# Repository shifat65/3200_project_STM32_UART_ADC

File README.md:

# STM32F103C6 Dual MCU Communication(UART) Project

## Overview

This project demonstrates UART communication, ADC threshold detection, timer-triggered transmissions, and external interrupt handling between two STM32F103C6 microcontrollers. The system is fully interrupt-driven and utilizes key peripherals including UART, ADC, Timers, SysTick, and GPIO.

## Features

### UART Communication (Between Two STM32F103C6 MCUs)
- **Transmit Indicator:** PA0 blinks when data is sent.
- **Receive Indicator:** PA1 blinks when data is received.
- **USART1 (PA9/PA10)** is used for UART communication.

### Timer-Based Data Transmission
- Timer triggers data transmission (values 0 to 3 cyclically) every 3 seconds.
- **Indicators:**
  - **PA4:** Displays the LSB of the transmitted data.
  - **PA7:** Displays the MSB of the transmitted data.

### Photoresistor Reading & Threshold Detection
- Reads analog input from a photoresistor connected to PB0.
- **High Threshold:** Turns ON PA5.
- **Low Threshold:** Turns OFF PA5 on the receiving MCU.

### External Interrupt Handling
- **PA2:** Configured for external interrupt input.
- On interrupt trigger via push button, a signal is sent to the other MCU.
- The second MCU toggles **PA6** in response.

## Hardware Used

- **2× STM32F103C6** microcontrollers (Blue Pill boards)
- **LEDs** (connected to GPIO pins for indication)
- **Photoresistor (LDR)** connected to PB0 for ADC input
- **Push Button** for triggering external interrupt on PA2
- **Breadboard** for prototyping
- **Jumper Wires** for connections
- **ST-Link Programmer** for flashing code

## STM32F103C6 Peripherals Used

- UART (USART1)
- ADC1 with Analog Watchdog
- General-purpose Timer (TIM2)
- SysTick Timer
- External Interrupt (EXTI2)
- GPIO (Input/Output)
- All operations are interrupt-driven

## Pin Configuration

| Pin    | Purpose                                  | Configuration                | CNF[1:0] + MODE[1:0] |
|--------|------------------------------------------|------------------------------|----------------------|
| PA0    | TX Indicator (Blink)                     | GPIO Output Push-Pull        | 0011                 |
| PA1    | RX Indicator (Blink)                     | GPIO Output Push-Pull        | 0011                 |
| PA2    | External Interrupt Input (Push Button)   | GPIO Input Pull-up/down      | 1000                 |
| PA4    | LSB Indicator of Sent Data               | GPIO Output Push-Pull        | 0011                 |
| PA5    | ADC Threshold Output                     | GPIO Output Push-Pull        | 0011                 |
| PA6    | External Interrupt Response (Toggle)     | GPIO Output Push-Pull        | 0011                 |
| PA7    | MSB Indicator of Sent Data               | GPIO Output Push-Pull        | 0011                 |
| PA9    | UART TX (USART1_TX)                      | Alternate Function Push-Pull | 1011                 |
| PA10   | UART RX (USART1_RX)                      | Input Floating               | 0100                 |
| PB0    | Photoresistor Input (ADC)                | Analog Input                 | 0000                 |

## Project Structure

### Initialization Functions

1. `void En_clock(void)`  
   Enables peripheral clocks for USART1, GPIO ports, TIM2, and ADC1.

2. `void gpio_setup(void)`  
   Configures GPIOs for UART, ADC input, external interrupts, and indicators.

3. `void systick_config(void)`  
   Configures SysTick for 1 ms tick using a 72 MHz system clock.

4. `void delay_ms(void)` and `void delay(uint32_t count)`  
   Delay utilities based on SysTick polling.

5. `void Uart1_config(void)`  
   Initializes USART1:
   - Baud Rate: 9600
   - Enables Tx, Rx, and RXNE interrupt
   - GPIO setup for PA9/PA10

6. `void ADC_config(void)`  
   Sets up ADC1 with:
   - Channel 8 (PB0)
   - Continuous conversion
   - Analog watchdog with threshold interrupts

7. `void timer_config(void)`  
   Configures TIM2:
   - Prescaler: 7200
   - Auto-reload: 50000
   - Triggers interrupt every 5 seconds

### Interrupt Handlers

- `void TIM2_IRQHandler(void)`  
  - Sends data via UART
  - Toggles PA0
  - Updates PA4 and PA7 to show LSB/MSB

- `void USART1_IRQHandler(void)`  
  - Handles received UART data
  - Updates GPIO indicators based on data

- `void ADC1_2_IRQHandler(void)`  
  - Compares ADC value to high/low thresholds
  - Sends specific character over UART depending on value range

- `void EXTI2_IRQHandler(void)`  
  - Responds to external interrupt on PA2
  - Sends a signal via UART
  - Toggles PA0

### Main Function

- `int main(void)`
  - Calls all setup functions
  - Enters an infinite loop
  - All runtime operations are interrupt-driven

## Circuit Diagram

## Build & Flash Instructions (Keil µVision 5)

1. Open the project in **Keil µVision 5** (`.uvprojx` file).
2. Set the target device to **STM32F103C6**.
3. Ensure correct startup file and system clock settings (72 MHz).
4. Build the project: **Project > Build Target** or press **F7**.
5. Connect the board using **ST-Link**.
6. Flash the firmware: **Flash > Download** or press **Ctrl + F8**.

### Tools Required

- Keil µVision 5 IDE
- STM32F1 Series Device Pack (via Keil Pack Installer)
- ST-Link USB Programmer 
- Optional: Logic analyzer or oscilloscope for UART debug

## Notes

- Use the same UART settings on both MCUs.
- Connect both boards with a common GND.
- Push button should be debounced or used with delay to avoid noise.
- ADC thresholds should match the characteristics of your photoresistor and ambient light conditions.

## License

This project is created for academic and educational purposes under the CSE 3200 course. No open-source license is currently applied.

## Author

*Syed Shifat E Rahman*

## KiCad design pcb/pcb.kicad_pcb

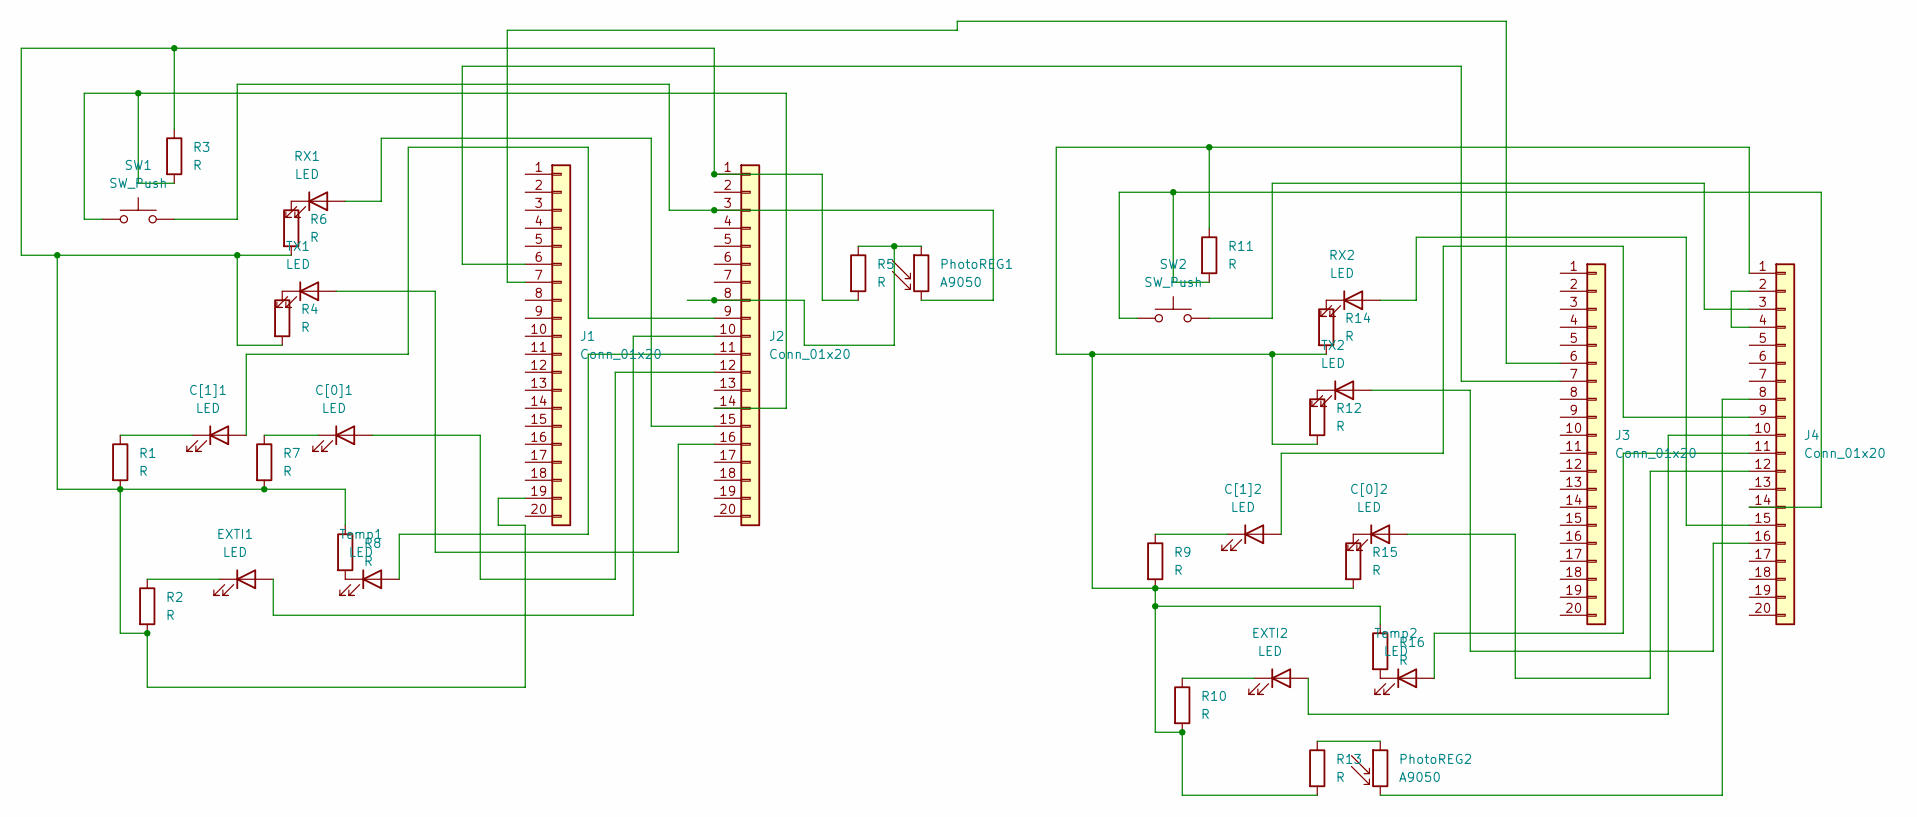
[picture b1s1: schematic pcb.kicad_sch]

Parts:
C[0]1, C[0]2, C[1]1, C[1]2: LED; LED_D3.0mm
EXTI1, EXTI2: LED; LED_D3.0mm
J1, J2, J3, J4: Conn_01x20; PinSocket_1x20_P2.54mm_Vertical
PhotoREG1, PhotoREG2: A9050; R_LDR_D6.4mm_P3.4mm_Vertical
R1, R2, R3, R4, R5, R6, R7, R8, R9, R10, R11, R12, R13, R14, R15, R16: R; R_Axial_DIN0204_L3.6mm_D1.6mm_P2.54mm_Vertical
RX1, RX2: LED; LED_D3.0mm
SW1: SW_Push; SW_PUSH-12mm_Wuerth-430476085716
SW2: SW_Push; SW_PUSH_1P1T_6x3.5mm_H5.0_APEM_MJTP1250
TX1, TX2: LED; LED_D3.0mm
Temp1, Temp2: LED; LED_D3.0mm

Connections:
unnamed: C[0]1.2 (A), J2.12
unnamed: C[0]1.1 (K), R7.1
unnamed: C[0]2.2 (A), J4.12
unnamed: C[0]2.1 (K), R15.1
unnamed: C[1]1.2 (A), J2.9
unnamed: C[1]1.1 (K), R1.1
unnamed: C[1]2.2 (A), J4.9
unnamed: C[1]2.1 (K), R9.1
unnamed: EXTI1.2 (A), J2.10
unnamed: EXTI1.1 (K), R2.1
unnamed: EXTI2.2 (A), J4.10
unnamed: EXTI2.1 (K), R10.1
unnamed: J1.6, J3.7
unnamed: J1.7, J3.6
unnamed: J1.19, J2.1, R1.2, R2.2, R3.1, R4.2, R5.2, R6.2, R7.2, R8.1
unnamed: J2.3, PhotoREG1.2, SW1.2
unnamed: J2.8, PhotoREG1.1, R5.1
unnamed: J2.11, Temp1.2 (A)
unnamed: J2.14, R3.2, SW1.1
unnamed: J2.15, RX1.2 (A)
unnamed: J2.16, TX1.2 (A)
unnamed: J4.1, R9.2, R10.2, R11.1, R12.2, R13.2, R14.2, R15.2, R16.1
unnamed: J4.2, J4.4
unnamed: J4.3, SW2.2
unnamed: J4.8, PhotoREG2.2
unnamed: J4.11, Temp2.2 (A)
unnamed: J4.14, R11.2, SW2.1
unnamed: J4.15, RX2.2 (A)
unnamed: J4.16, TX2.2 (A)
unnamed: PhotoREG2.1, R13.1
unnamed: R6.1, RX1.1 (K)
unnamed: R14.1, RX2.1 (K)
unnamed: R4.1, TX1.1 (K)
unnamed: R12.1, TX2.1 (K)
unnamed: R8.2, Temp1.1 (K)
unnamed: R16.2, Temp2.1 (K)

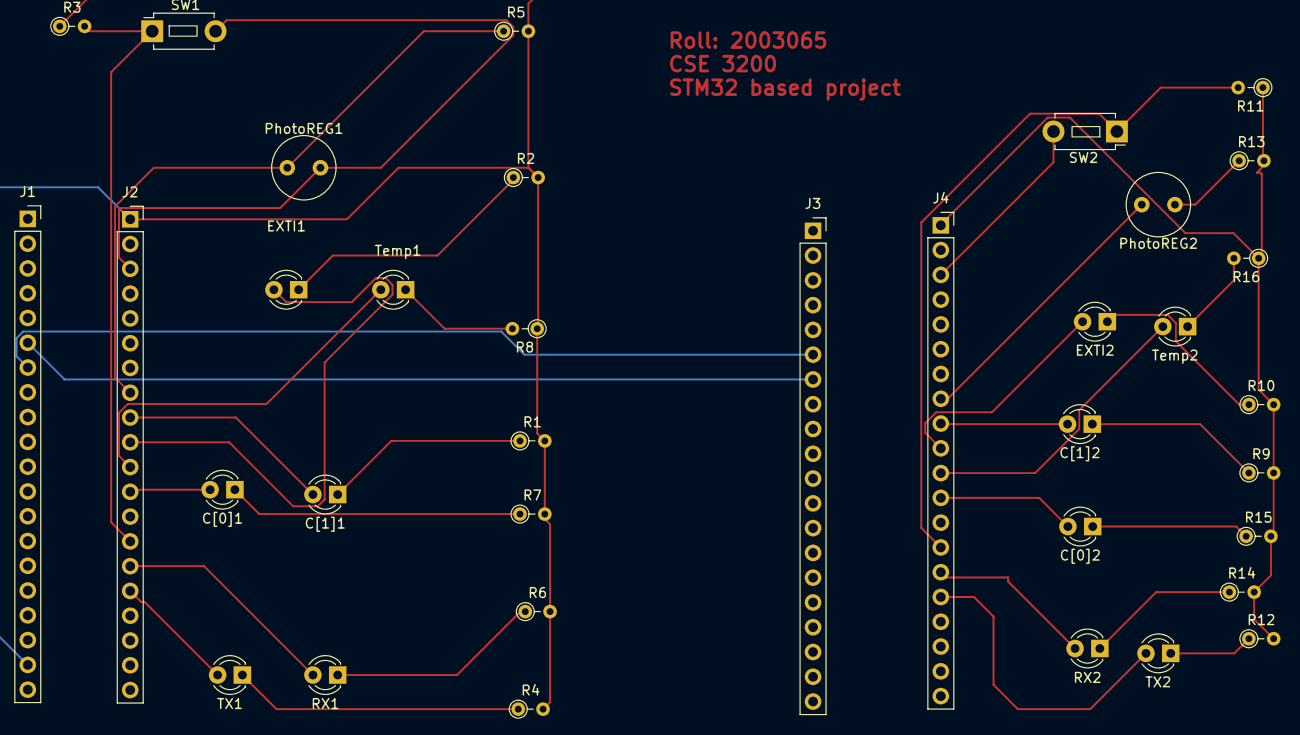
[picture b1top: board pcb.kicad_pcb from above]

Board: 2 copper layers, 36 parts (0 on the bottom side), 36 nets.

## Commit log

2025-06-23 Systick and Timer config
2025-06-23 Basic file update
2025-06-23 Implementation of USART on GPIO Time Interrupt. Receive USART data using USART Interrupt
2025-06-23 Config UART2 with UART1
2025-06-24 ADC added with interrupt
2025-06-24 Passing value of ADC through UART(has some error led blinks random
2025-06-28 Redesign: USART with timer
2025-06-28 USART with timeer and ExT Interrupt
2025-06-28 Only ADC
2025-06-28 Final: USART, ExT interrupt, ADC, Timer
2025-06-28 Circuit diagram Added
2025-07-17 Manual added
